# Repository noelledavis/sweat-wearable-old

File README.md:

# Wearable Circuits Documentation

### Table of Contents
1. [What's in the repo?](#toolchain)
2. [Programming Toolchain](#programming)

### What's in the repo?

This repo contains the board designs, firmware, and accompanying documentation for the Eric 4.0 and for the iontophoresis/sweat analysis projects. Documentation for each design is placed in the respective folder, and includes design notes, component datasheets, and programming instructions.

### Programming Toolchain

All of the firmware is written in C++ using the Arduino framework, compiled for the ATMega328P running at 16 MHz on a 5V supply. All of the code can be viewed/edited/compiled in the Arduino IDE (just copy the source into a new sketch).

I have been using [platformio](http://platformio.org/) as my programming toolchain for firmware, and the repo is currently set up for easy compilation and programming using platformio, GNU Make, and the Unix command line. To take advantage of this, install platformio and make sure that the board "pro16MHzatmega328" is installed. After installing platformio, you can use Make to compile the code and to program the microcontroller directly from the command line.

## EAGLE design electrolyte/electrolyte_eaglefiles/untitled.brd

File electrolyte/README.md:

# Iontophoresis + Electrolyte Board Documentation

## Table of Contents
1. [What's in here?](#what)
2. [How to use the board](#how)
3. [Board Architecture](#boardarch)
4. [Physical board layout](#replace)
5. [Firmware and command spec](#command)
6. [Programming instructions](#program)

## What's in here? <div id='what'/>

This folder contains the board design and all of the supporting information for ordring more copies of the iontohphoresis + electrolyte sensing board. It also conatains the firmware for the board, and the datasheets for all of the components.

* **electrolyte_board_datasheets** contains the datasheets for all of the components
* **electrolyte_r3_orderfiles** contains the files needed to order and auto-assemble another round of the iontophoresis + electrolyte board. Included are the gerber files, as well as the centroids file and the Bill of Materials.
* **electrolyte_firmware_FINAL** contains the firmware for the board
* **electrolyte_eaglefiles** contains the Eagle CAD files for the board design. The associated libraries are found in the parent folder under **../eagle_libs**.

## How to use the board? <div id='how'/>

### Supplying power

The board is powered off of a single 3.7V battery, or by a power supply with a minimum output voltage of around 3.5V. **Take care to not let the battery voltage fall too far, as one of the switching regulators on the board has the tendency to heat up a lot if its input voltage is too low.** The current draw on a 4V power supply should be around 0.1A. The pinout for the battery connector is shown below:

### Connecting to Bluetooth

The board can be connected to using Bluetooth (both the GetBlue app and the custom app should work). The baud rate is 9600, and this cannot be changed. Data should be streaming out of the board as soon as a connection is made. The default pairing password for these Bluetooth modules is 1234.

**When trying to control the board using the GetBlue app, make sure that the output of GetBlue is hexadecimal.**

### Using Bluetooth commands

The board receives 8-bit commands over Bluetooth. The baud rate is 9600. When transmitting Bluetooth commands make sure that the commands are sent as bytes or hex values. Sending data as a string will be misinterpreted. The commands have format

The opcode determines what the command is, and the payload is a 4-bit number containing data. 

The board has two modes, sensing mode and current mode:

#### Sensing mode

In sensing mode, the board continuously dumps out sensor readings and current values in text string lines with the format

```
SensorCh1,SensorCh2,Current delivered,Current register
```

In this mode, the sensing switches are closed, enabling sensing, and the iontophoresis switches are open, for safety. The sensor readings are valid, the current delivered should be near zero, and current register should be exactly zero. The sensor readings are given in millivolts (mV), and the current delivered reading is given in microamps (uA).

#### Current mode

In current mode, the board continuously dumps out current values and placeholders for sensor readings in the format

```
x,x,Current delivered,Current register
```

In this mode, the sensing switches are open, disabling sensing, and the iontophoresis switches are closed. The current delivered is proportional to the 8-bit current register value. The current delivered reading is given in microamps (uA).

#### Bluetooth command specifications

Name                                   |  Hex   | Function
:-------------------------------------:|:------:|:-------------------------:
DISABLE\_IONTOPHORESIS                 |  0x4   | Disables iontophoresis, puts the board back into sensing mode.
ENABLE\_IONTOPHORESIS\_INCREMENT\_BY   | 0x5    | Adds the payload bits to the iontophoresis PWM value. Has overflow protection. Puts the board into iontophoresis mode automatically.
ENABLE\_IONTOPHORESIS\_DECREMENT\_BY   | 0x6    | Subtracts the payload from the iontophoresis PWM value. Has underflow protection. Takes the board into sensing mode automatically if PWM value reaches 0.

### Which channel is which?

Looking down from the top, with components facing up:

## Board Architecture <div id='boardarch'/>

### Voltage channels

The board has two voltage sensor channels. The analog supply voltage VDDA is 5V. The voltage sensor channels have the following architecture.

The frontend instrumentation amplifier is an Analog Devices AD8422, which was chosen specifically for its low input bias current and corresponding very high input impedance. The - terminal of the instrumentation amplifier is "floating", and is held to near 2.5V by a 10k resistor. This resistor was chosen empirically, and is large enough to be swapped by hand (described later). The reference terminal of the instrumentation amplifier is held to 2.5V to center the output of the instrumentation amplifier around 2.5V (i.e. a 0V difference across the sensor will lead to an output of 2.5V at the instrumentation amplifier). The gain resistor is chosen to be 5k, for an approximate voltage gain of 5.

The second stage of the circuit consists of two cascaded Sallen-Key low-pass filters. The passives are set such for a fourth-order low pass filter with the cutoff frequency set at 1Hz. The op-amps for the filters were chosen to be LT6005 quad general-purpose op-amps, chosen mainly for low power consumption and small size. The output of the second stage is connected directly to one of the channels of the ATMega328P ADC.

The switches placed in front of the instrumentation amplifer input terminals are ADG711 analog switches. **These switches are required to be in the OPEN state when iontophoresis is being run, to eliminate the risk of skin burns through the sensing electrodes**. The ADG711 was chosen for its ultra-low source-drain leakage current, which is necessary for the sensors to function properly.

### Power distribution

The overall system is powered off of a single 3.7V lithium ion battery. The following figure shows the power distribution for the system:

* An LTC3525-5 switching regulator is connected to the battery, and outputs 5V. This regulator is used to power both the analog components and the digital components.
* One TLE2426 rail-splitter. This is connected to the output of the 5V 
voltage regulator to provide virtual ground at 2.5V.
* A 3.3V LDO regulator is connected to the battery, and is used to power the Bluetooth module.
* An LMR64010 boost regulator is connected to the battery, and the feedback resistors are set such that the component outputs +40V for the iontophoresis power supply.

### Iontophoresis current source

The iontophoresis current source consists of a current DAC controlled by a PWM voltage output from the microcontroller. The overall schematic for the iontophoresis current source is shown below:

The PWM output from the microcontroller is passed through a second order low pass filter and then buffered. This serves to convert the PWM wave into its DC average value, and acts as a low-frequency voltage DAC for driving the current DAC. 

The difference amp and output BJT act as a voltage-controlled current source. The arithmetic demonstrating this is worked out in currentsource.pdf.

At the output of the current source, a high-side shunt amplifier based on the INA282 is used to monitor the current in real time. The output of the INA282 is connected to one of the channels of the microcontroller ADC, and is used to make sure that the true output of the current source circuit is close to its programmed value.

A current-limiting circuit is placed after the shunt amplifier, consisting of the MMBF5457 JFET and a series resistor. To raise the current limit, this resistor's value can be set lower (i.e. around 250 Ohm). To lower the current limit, the resistor's value can be set higher (up to around 750 Ohm).

Lastly, an analog switch is placed after the current-limiting circuit, to ensure that current can be fully shut off and to ensure that the iontophoresis circuit does not affect the sensors. The switch was chosen to be an ADG5401, because of its large range of supply voltages (up to 40V). Note that the node at the output of the iontophoresis circuit can swing up as high as around 36V with an open circuit load.

The current DAC can output around 1.2 mA for a wide range of physiological load resistances.

### Bluetooth

The Bluetooth module is an HC-06. These particular modules are quite common among hobbyists, and can be easily obtained off of Amazon. The Bluetooth modules enter bypass mode as soon as a connection is made, so nothing clever needs to be done in the ATMega328P firmware to get the Bluetooth module to work. The baud rate is 9600.

## Board layout <div id='replace'/>

The overall board layout is shown below:

### User replaceable parts

* The Bluetooth module must be hand-installed. The HC-06 Bluetooth module usually comes soldered to a larger baseboard, and you must first desolder the module from the baseboard before installing it onto the iontophoresis + electrolyte board.
* Resistor R27 is the resistor used to set the current limit. By default, this resistor is around 250 Ohm, but can be raised higher (up to around 750 Ohm) for a lower current limit. 

## Firmware and command spec <div id='command'/>

The commands for controlling the electrolyte board over Bluetooth are described in the document **electrolyte_bt_commands/bluetooth_spec.pdf**. Note that the commands consist of two hexadecimal digits. The first hexadecimal digit corresponds to an opcode, and the second hexadecimal digit usually corresponds to an immediate.

The firmware is written like a finite-state-machine. The state variables are
* `iontophoresisStatsuBits`, corresponding to a bitmask determining whether iontophoresis is enabled or not. This state variable affects the states of the switches.
* `measurementStatusBits`, corresponding to a bitmask determining what ADC values to read back, if any.
* `iontophoresisCurrentValue`, corresponding to the 8-bit number (0-255) proportional to the amount of iontophoresis current that should be delivered.

The inputs to the FSM are the commands.

## Programming instructions <div id='program'/>

There are six header pads directly underneath the microcontroller. **Flipping over the board**, and placing it in the orientation described in the image on the left,

Board bottom pinout                             |  Sparkfun Programmer
:----------------------------------------------:|:-------------------------:
  |  

connect the pins of the programmer to the correspondingly labeled pads. **Note that the layout of the programmer pins is different from that of the Eric4.0.** You will most likely have to solder wires to the pads on the amplifier board to achieve this. I suggest using female jumper wires to connect the programmer to these wires. The image on the right shows the pinout of the Sparkfun programmer board.

Open up the Arduino IDE, and make sure the following things are set:
* Board is set to "Arduino Pro" or "Arduino Pro Mini"
* Programmer is USBtinyISP
* Processor is set to ATMega328, 5V 16MHz

If you are programming a board for the very first time, make sure you run "Burn the Bootloader" or else the code won't work. This seems to be the most foolproof way to make sure that the fuses are set to the correct values.

Then, from the Arduino IDE, you can click "Upload using programmer" to put the code onto the microcontroller.

Alternatively, if you have platformio and GNU Make installed, you can run
```
make
```
to compile the code and
```
make impact
```
to copy the code onto the microcontroller. **I have not figured out how to burn fuse values through platformio, so you're going to have to open up the Arduino IDE to do that.**

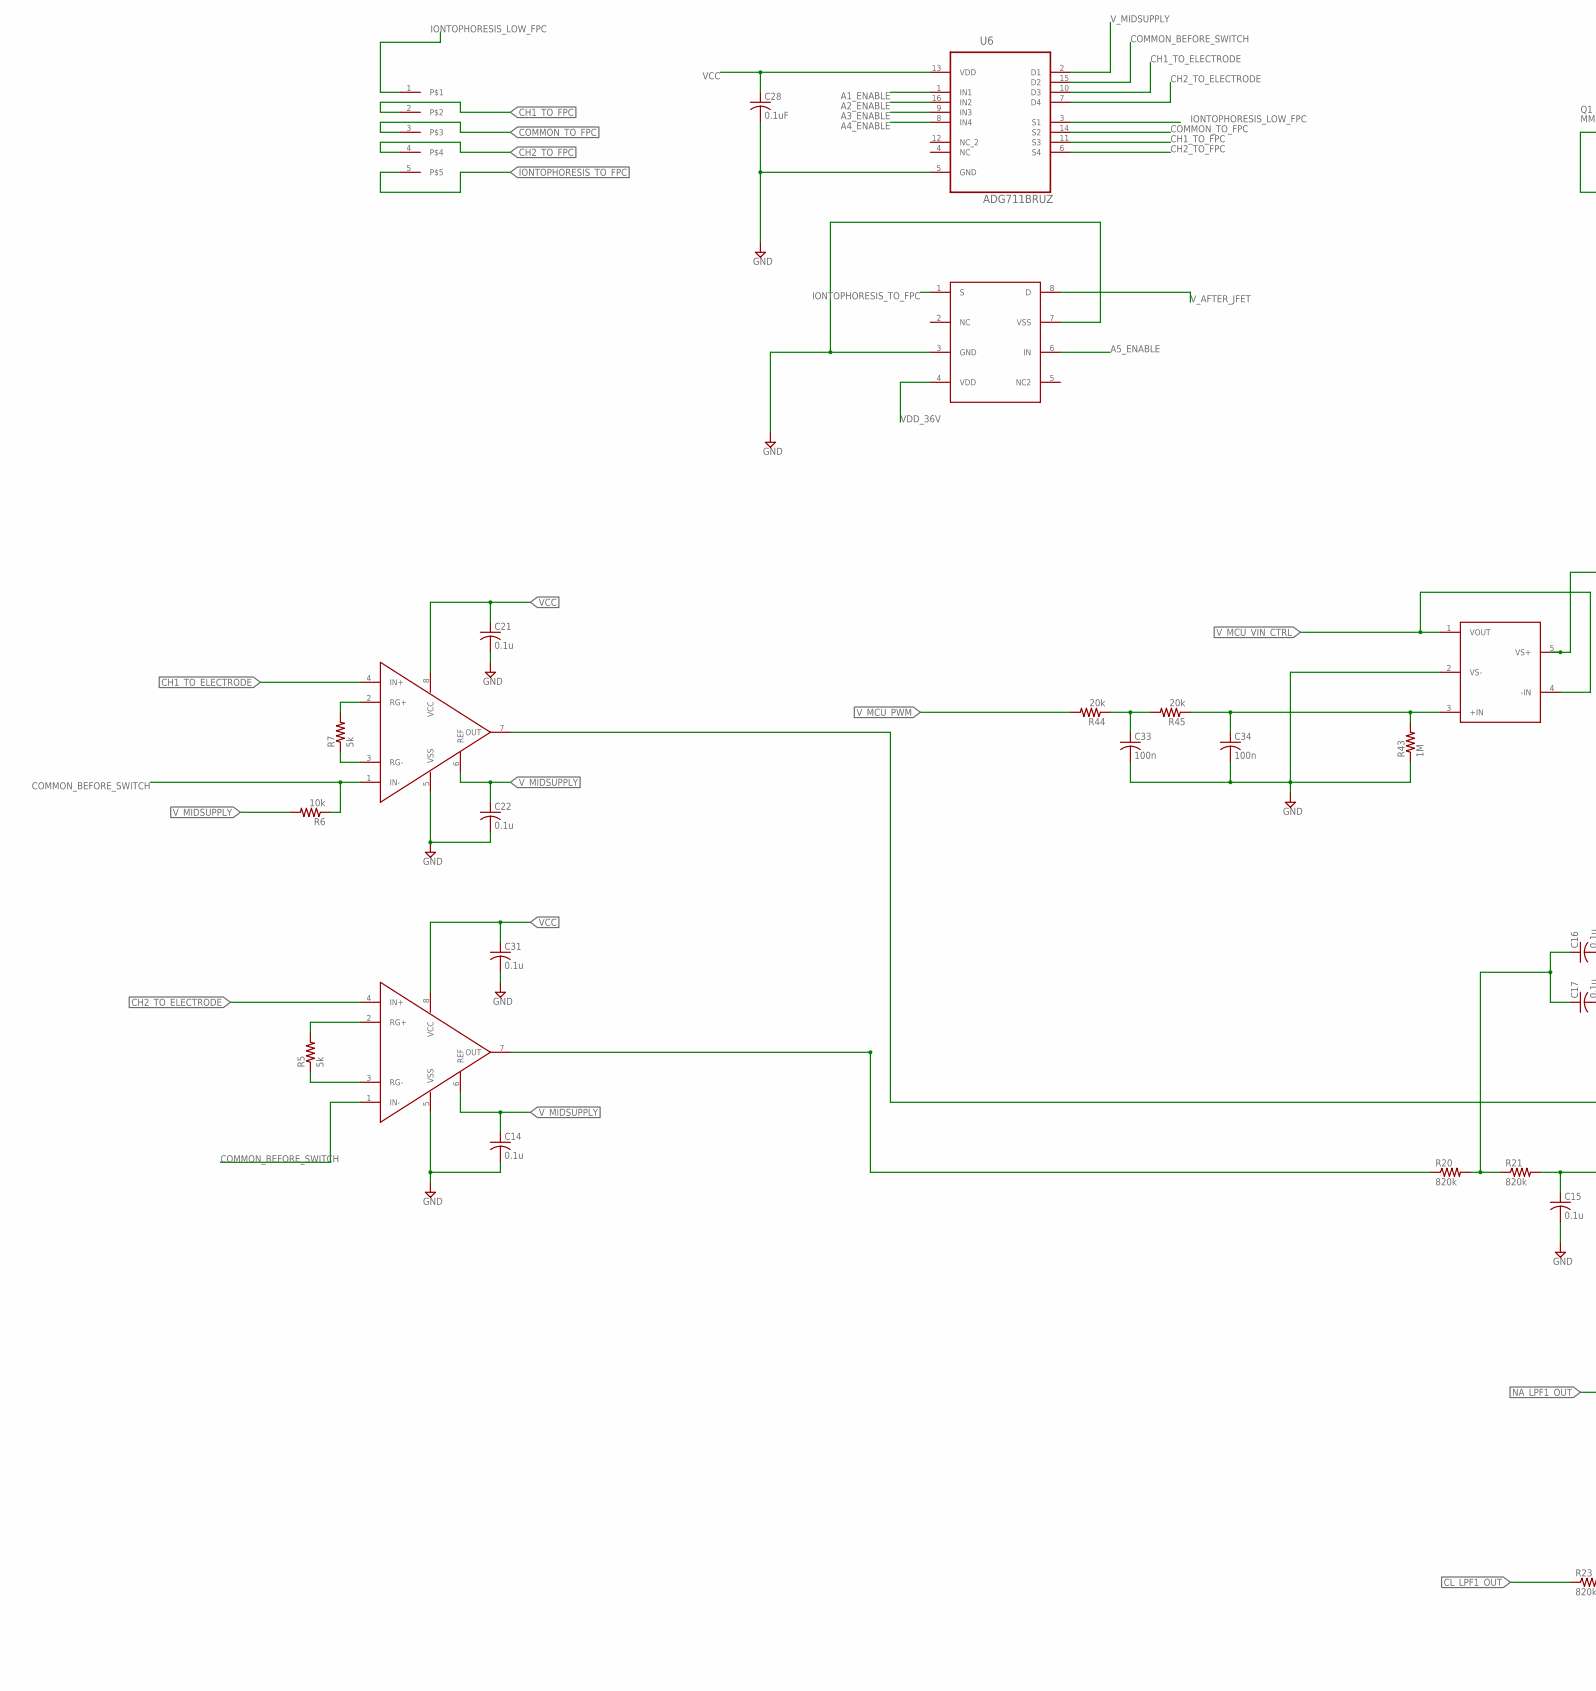
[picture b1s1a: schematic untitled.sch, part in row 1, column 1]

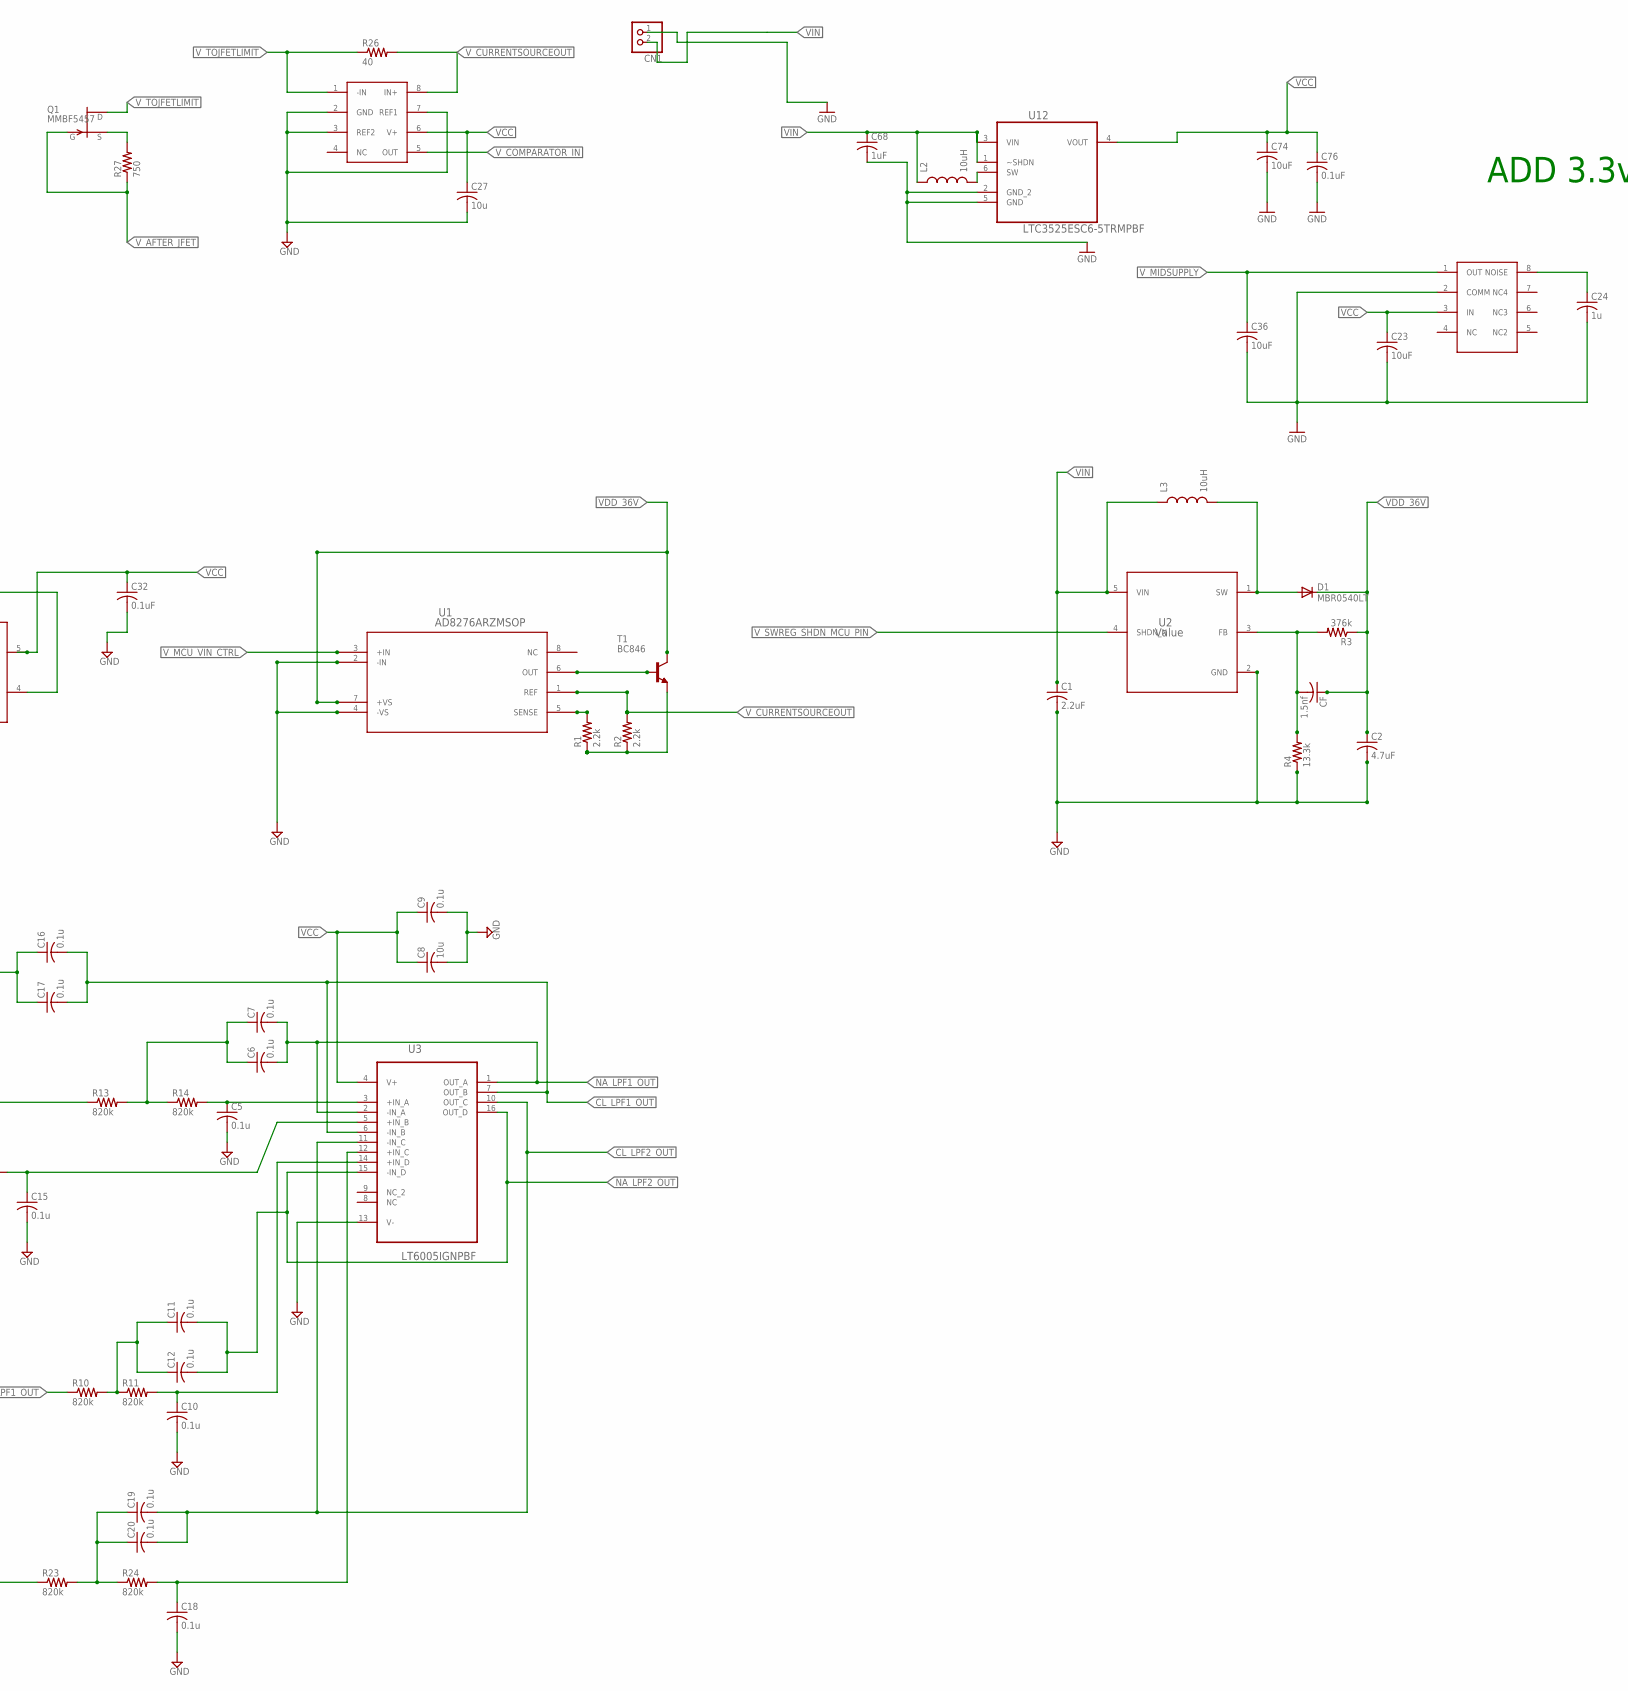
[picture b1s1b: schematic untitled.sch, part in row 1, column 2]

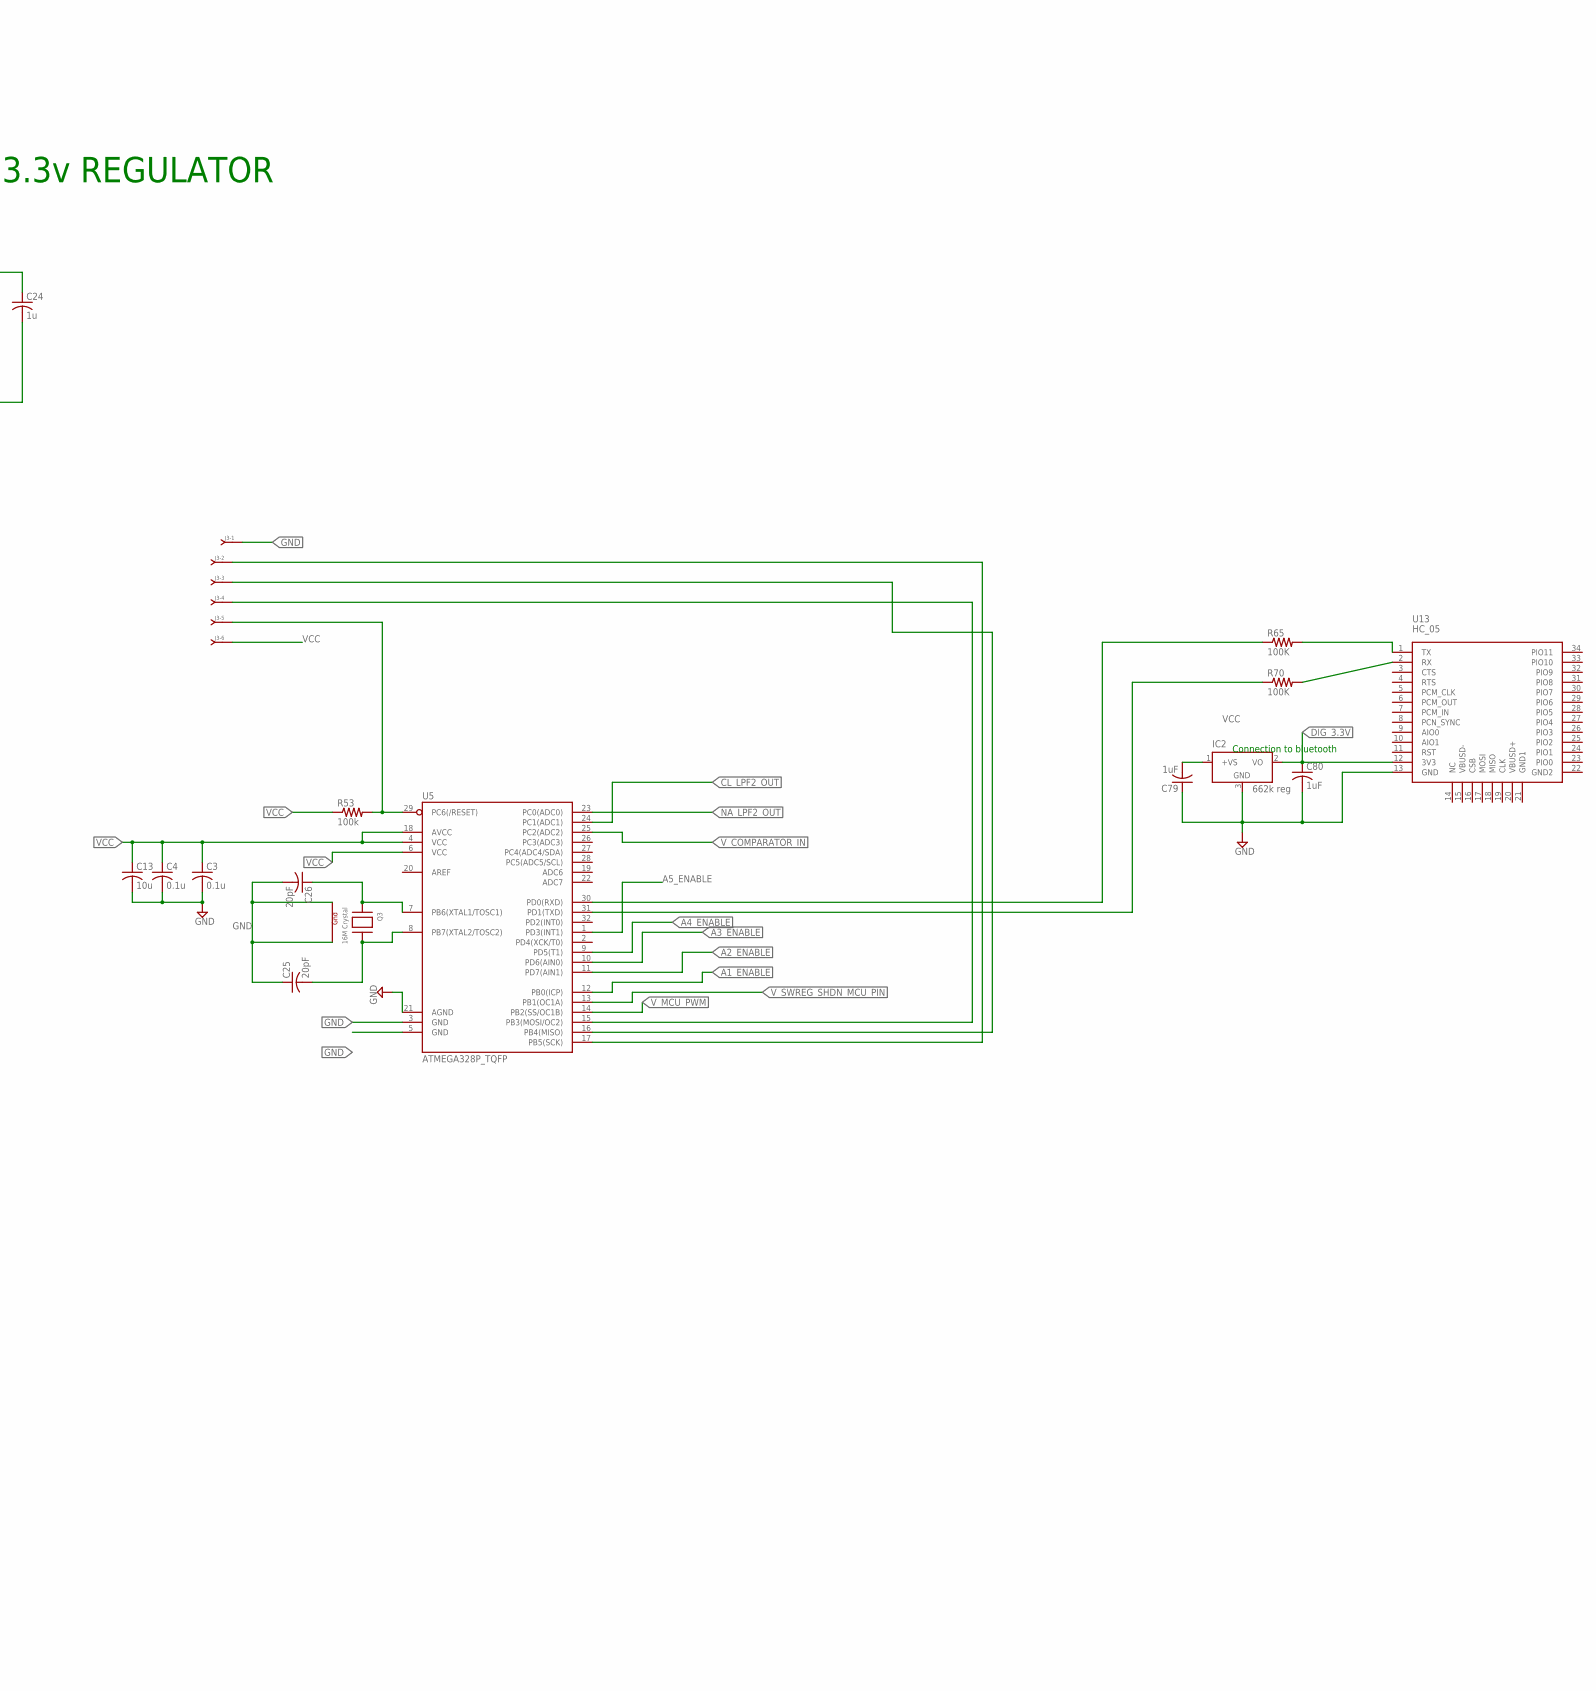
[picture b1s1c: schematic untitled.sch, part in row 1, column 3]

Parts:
C1: 2.2uF; C0402
C2: 4.7uF; C0603
C3, C4, C5, C6, C7, C9, C10, C11, C12, C14, C15, C16, C17, C18, C19, C20, C21, C22, C31: 0.1u; C0201
C8, C13, C27: 10u; C0402
C23, C36, C74: 10uF; C0402
C24: 1u; C0402
C25, C26: 20pF; C0402
C28, C32: 0.1uF; C0201
C33, C34: 100n; C0201
C68, C79, C80: 1uF; C0402; MPN MC0402X105M6R3CT
C76: 0.1uF; C0402
CF: 1.5nf; C0402
CN1: JST_2PIN-SMT; JST-PH-2-SMT
D1: MBR0540LT; SOD123
IC2: 662k reg; SOT23; MPN LM5008MM/NOPB
J3: J-06-100-2X03; HDR-100-2X03
L2, L3: 10uH; 0805
Q1: MMBF5457; SOT23
Q3: 16M Crystal; NX3225
R1, R2: 2.2k; R0201
R3: 376k; R0402
R4: 13.3k; R0402
R5, R7: 5k; R0201
R6: 10k; R0201
R10, R11, R13, R14, R20, R21, R23, R24: 820k; R0201
R26: 40; R0201
R27: 750; R0402
R43: 1M; R0201
R44, R45: 20k; R0201
R53: 100k; R0201
R65, R70: 100K; R0201
T1: BC846; SOT23
U1: AD8276ARZMSOP; MSOP08
U2: Value; DBV0005A_N
U3: LT6005IGNPBF; SOP63P600X175-16N
U4: INA282; SO08
U5: ATMEGA328P_TQFP; TQFP32-08
U6: ADG711BRUZ; SOP65P640X120-16N
U7, U8: SOIC8_INAMPMSOP; MSOP08
U12: LTC3525ESC6-5TRMPBF; SOT65P210X100-6N
U13: HC_05; BLUETOOTH_SMD
U15: TLE2426IDR; R_8
U20: FH12-5S-1SH
U$1: ADG5401; MSOP08
U$5: LT1800; SOT23-5

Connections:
A1_ENABLE: U5.12 (PB0(ICP)), U6.1 (IN1)
A2_ENABLE: U5.11 (PD7(AIN1)), U6.16 (IN2)
A3_ENABLE: U5.10 (PD6(AIN0)), U6.9 (IN3)
A4_ENABLE: U5.9 (PD5(T1)), U6.8 (IN4)
A5_ENABLE: U5.1 (PD3(INT1)), U$1.6 (IN)
CH1_TO_ELECTRODE: U6.10 (D3), U7.4 (IN+)
CH1_TO_FPC: U6.11 (S3), U20.2
CH2_TO_ELECTRODE: U6.7 (D4), U8.4 (IN+)
CH2_TO_FPC: U6.6 (S4), U20.4
CL_LPF1_OUT: C16.2, C17.2, R23.1, U3.6 (-IN_B), U3.7 (OUT_B)
CL_LPF2_OUT: C19.2, C20.2, U3.10 (OUT_C), U3.11 (-IN_C), U5.24 (PC1(ADC1))
COMMON_BEFORE_SWITCH: R6.1, U6.15 (D2), U7.1 (IN-), U8.1 (IN-)
COMMON_TO_FPC: U6.14 (S2), U20.3
DIG_3.3V: C80.1, IC2.2 (VO), U13.12 (3V3)
GND: C1.2, C2.2, C3.2, C4.2, C5.2, C8.2, C9.2, C10.2, C13.2, C14.2, C15.2, C18.2, C21.2, C22.2, C23.2, C24.2, C25.1, C26.2, C27.2, C28.2, C31.2, C32.2, C33.2, C34.2, C36.2, C68.2, C74.2, C76.2, C79.1, C80.2, CN1.1 (2), IC2.3 (GND), J3.1, Q3.2 (G2), Q3.4 (G1), R4.1, R43.1, U1.2 (-IN), U1.4 (-VS), U2.2 (GND), U3.13 (V-), U4.2 (GND), U4.3 (REF2), U4.7 (REF1), U5.3 (GND), U5.5 (GND), U5.21 (AGND), U6.5 (GND), U7.5 (VSS), U8.5 (VSS), U12.2 (GND_2), U12.5 (GND), U13.13 (GND), U15.2 (COMM), U$1.3 (GND), U$1.7 (VSS), U$5.2 (VS-)
IONTOPHORESIS_LOW_FPC: U6.3 (S1), U20.1
IONTOPHORESIS_TO_FPC: U20.5, U$1.1 (S)
unnamed: T1.1 (B), U1.6 (OUT)
unnamed: R13.1, U7.7 (OUT)
unnamed: R1.2, U1.5 (SENSE)
unnamed: R1.1, R2.1, T1.2 (E)
unnamed: R20.1, U8.7 (OUT)
unnamed: R5.1, U8.3 (RG-)
unnamed: CF.2, R3.2, R4.2, U2.3 (FB)
unnamed: R5.2, U8.2 (RG+)
unnamed: R65.1, U5.30 (PD0(RXD))
unnamed: C10.1, R11.2, U3.14 (+IN_D)
unnamed: C5.1, R14.2, U3.3 (+IN_A)
unnamed: Q1.2 (S), R27.2
unnamed: C6.1, C7.1, R13.2, R14.1
unnamed: C11.1, C12.1, R10.2, R11.1
unnamed: R7.1, U7.3 (RG-)
unnamed: R7.2, U7.2 (RG+)
unnamed: C24.1, U15.8 (NOISE)
unnamed: C15.1, R21.2, U3.5 (+IN_B)
unnamed: C16.1, C17.1, R20.2, R21.1
unnamed: C18.1, R24.2, U3.12 (+IN_C)
unnamed: C19.1, C20.1, R23.2, R24.1
unnamed: J3.5, R53.2, U5.29 (PC6(/RESET))
unnamed: L2.2, U12.6 (SW)
unnamed: C25.2, Q3.3 (X2), U5.8 (PB7(XTAL2/TOSC2))
unnamed: C34.1, R43.2, R45.1, U$5.3 (+IN)
unnamed: C33.1, R44.1, R45.2
unnamed: C26.1, Q3.1 (X1), U5.7 (PB6(XTAL1/TOSC1))
unnamed: R65.2, U13.1 (TX)
unnamed: J3.4, U5.15 (PB3(MOSI/OC2))
unnamed: J3.2, U5.17 (PB5(SCK))
unnamed: J3.3, U5.16 (PB4(MISO))
unnamed: R70.1, U5.31 (PD1(TXD))
unnamed: R70.2, U13.2 (RX)
NA_LPF1_OUT: C6.2, C7.2, R10.1, U3.1 (OUT_A), U3.2 (-IN_A)
NA_LPF2_OUT: C11.2, C12.2, U3.15 (-IN_D), U3.16 (OUT_D), U5.23 (PC0(ADC0))
PIN1: D1.A, L3.2, U2.1 (SW)
VCC: C3.1, C4.1, C8.1, C9.1, C13.1, C21.1, C23.1, C27.1, C28.1, C31.1, C32.1, C74.1, C76.1, C79.2, IC2.1 (+VS), J3.6, R53.1, U3.4 (V+), U4.6 (V+), U5.4 (VCC), U5.6 (VCC), U5.18 (AVCC), U6.13 (VDD), U7.8 (VCC), U8.8 (VCC), U12.4 (VOUT), U15.3 (IN), U$5.5 (VS+)
VDD_36V: C2.1, CF.1, D1.C, R3.1, T1.3 (C), U1.7 (+VS), U$1.4 (VDD)
VIN: C1.1, C68.1, CN1.2 (1), L2.1, L3.1, U2.5 (VIN), U12.1 (~SHDN), U12.3 (VIN)
V_AFTER_JFET: Q1.3 (G), R27.1, U$1.8 (D)
V_COMPARATOR_IN: U4.5 (OUT), U5.25 (PC2(ADC2))
V_CURRENTSOURCEOUT: R2.2, R26.2, U1.1 (REF), U4.8 (IN+)
V_MCU_PWM: R44.2, U5.14 (PB2(SS/OC1B))
V_MCU_VIN_CTRL: U1.3 (+IN), U$5.1 (VOUT), U$5.4 (-IN)
V_MIDSUPPLY: C14.1, C22.1, C36.1, R6.2, U6.2 (D1), U7.6 (REF), U8.6 (REF), U15.1 (OUT)
V_SWREG_SHDN_MCU_PIN: U2.4 (SHDN_N), U5.13 (PB1(OC1A))
V_TOJFETLIMIT: Q1.1 (D), R26.1, U4.1 (-IN)

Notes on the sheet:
ADD 3.3v REGULATOR
Connection to bluetooth

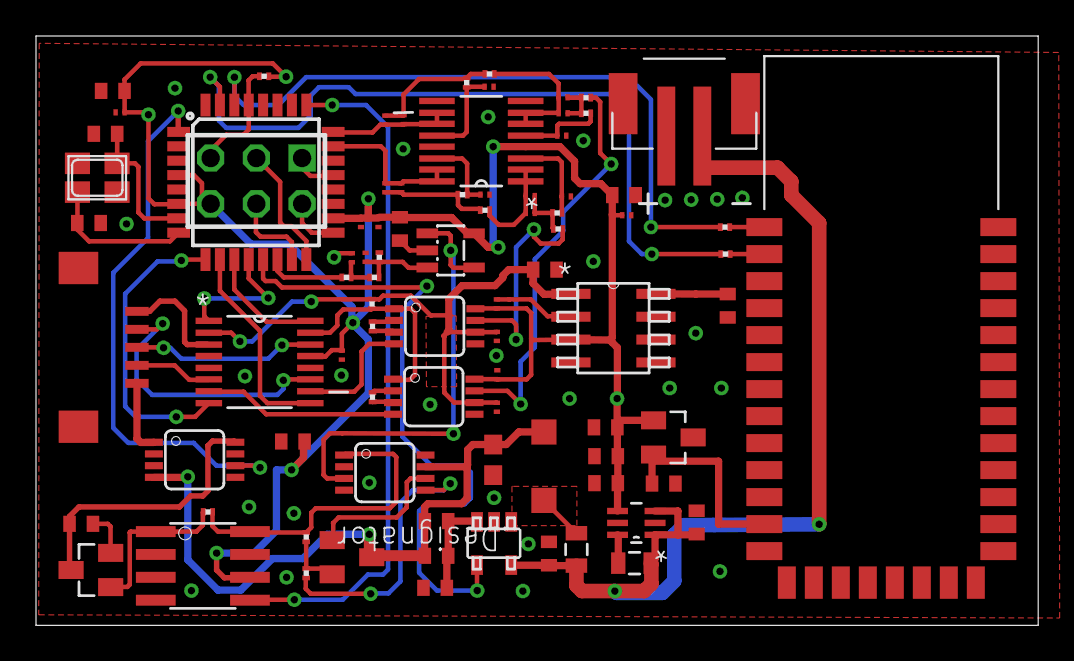
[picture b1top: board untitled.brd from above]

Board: 2 copper layers, 55.7 x 32.7 mm, 85 parts (0 on the bottom side), 64 nets.

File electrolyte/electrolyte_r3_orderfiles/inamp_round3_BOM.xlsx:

Item # | Quantity per board | Manufacturer Part # | Do Not Install | Reference designators | Vendor (optional) | Vendor Part Number (optional) | Value (optional) | Size / Footprint (optional) | Part description/ specs (optional, but recommended) | Manfacturer (optional)
1 | 1 | CRCW02011M00FNED |  | R43 | Digikey | 541-1.00MABCT-ND | 1M | R0201 |  | Vishay-Dale
2 | 1 | MMBF5457 |  | Q1 | Digikey | MMBF5457CT-ND | MMBF5457 N-channel JFET | SOT23 |  | Fairchild
3 | 2 | GRM1555C1H200JA01D |  | C25,C26 | Digikey | 490-5930-1-ND | 20pF | C0402 | 20pF capacitor | Murata
4 | 1 | CL05B152KB5NNNC |  | CF | Digikey | 1276-1521-1-ND | 1500pF | C0402 | 50V 1500pF capacitor | Samsung
5 | 1 | LMR64010XMFE/NOPB |  | U2 | Digikey | LMR64010XMFE/NOPBCT-ND |  | SOT23-5 |  | Texas Instruments
6 | 4 | GRM155R60J105KE19D |  | C24,C68,C79,C80 | Digikey | 490-1320-1-ND | 1uF | C0402 |  | Murata
7 | 1 | INA282AIDR |  | U4 | Digikey | 296-27820-1-ND |  | SOIC-8 |  | Texas Instruments
8 | 1 | LT6005IGN#PBF |  | U3 | Digikey | LT6005IGN#PBF-ND |  | 16-SSOP |  | Linear Technologies
9 | 1 | MBR0540L-TP |  | D1 | Digikey | MBR0540L-TPMSTR-ND |  | SOD123 | 40V Schottky diode | Micro Commercial
10 | 1 | MCR006YRTJ390 |  | R26 | Digikey | RHM39CCCT-ND | 39 | R0201 |  | Rohm Semiconductor
11 | 3 | MCR006YRTF1003 |  | R65,R70,R53 | Digikey | RHM100KCBCT-ND | 100k | R0201 |  | Rohm Semiconductor
12 | 1 | CL05A225MQ5NNNC |  | C1 | Digikey | 1276-1469-1-ND | 2.2uF | C0402 |  | Samsung
13 | 1 | ADG711BRUZ |  | U6 | Digikey | ADG711BRUZ-ND |  | 16TSSOP |  | Analog Devices
14 | 1 | BC846B,215 |  | T1 | Digikey | 568-1632-1-ND |  | SOT23 | 65V NPN BJT | NXP Semiconductors
15 | 1 | FH12-5S-1SH(55) |  | U20 | Digikey | HFB105CT-ND |  |  |  | Hirose
16 | 1 |  | DNI | R27
17 | 2 | MLZ2012M100WTD25 |  | L2,L3 | Digikey | 445-17073-1-ND | 10uH | 805 |  | TDK
18 | 1 | ERJ-2RKF1332X |  | R4 | Digikey | P13.3KLCT-ND | 13.3k | R0402 |  | Panasonic
19 | 6 | CL05A106MQ5NUNC |  | C8,C13,C23,C27,C36,C74 | Digikey | 1276-1451-1-ND | 10uF capacitor | C0402 |  | Samsung
20 | 1 | LTC3525ESC6-5#TRMPBF |  | U12 | Digikey | LTC3525ESC6-5#TRMPBFCT-ND |  | SC70 | 5V boost regulator | Linear Technologies
21 | 1 | LT1800CS5#TRMPBF |  | U$5 | Digikey | LT1800CS5#TRMPBFCT-ND |  | TSOT23-5 |  | Linear Technologies
22 | 8 | ERJ-1GEF8203C |  | R10,R11,R13,R14,R20,R21,R23,R24 | Digikey | P820KABCT-ND | 820k | R0201 |  | Panasonic
23 | 2 | RC0201JR-0720KL |  | R44,R45 | Digikey | 311-20KNCT-ND | 20k | R0201 |  | Yageo
24 | 1 | S2B-PH-SM4-TB(LF)(SN) |  | CN1 | Digikey | 455-1749-1-ND |  |  | JST-PH 2 pin connector | JST
25 | 23 | GRM033R60J104KE19D |  | C3,C4,C5,C6,C7,C9,C10,C11,C12,C14,C15,C16,C17,C18,C19,C20,C21,C22,C31,C32,C33,C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 | Digikey | 490-3167-1-ND | 0.1uF capacitor | C0201 |  | Murata
26 | 1 | ADG5401BRMZ |  | U$1 | Digikey | ADG5401BRMZ-ND |  |  |  | Analog Devices
27 | 1 | AP7313-33SAG-7 |  | IC2 | Digikey | AP7313-33SAG-7DICT-ND |  | SOT23 | 3.3V LDO | Diodes Incorporated
28 | 1 | GRM155R61A104KA01D |  | C76 | Digikey | 490-1318-1-ND | 0.1uF capacitor | C0402 |  | Murata
29 | 1 | C1608X5R1V475M080AC |  | C2 | Digikey | 445-9042-1-ND | 4.7uF capacitor | C0603 | 35V capacitor | TDK
30 | 2 | AD8422BRMZ |  | U7,U8 | Digikey | AD8422BRMZ-ND |  | 8-MSOP | Instrumentation amplifier | Analog Devices
31 | 1 | C0603X5R0J105M030BC |  | C30 | Digikey | 445-8008-1-ND | 1uF capacitor | C0201 |  | TDK
32 | 1 | AD8276ARMZ-R7 |  | U1 | Digikey | AD8276ARMZ-R7TR-ND |  | 8-MSOP |  | Analog Devices
33 | 1 | ATMEGA328P-AUR |  | U5 | Digikey | ATMEGA328P-AURCT-ND |  | 32-TQFP |  | Atmel
34 | 1 | NX3225SA-16.000000MHZ-T1 |  | Q3 | Digikey | 644-1100-1-ND |  |  | 16 MHz oscillator | NDK
35 | 2 | CRCW02012K20FKED |  | R1,R2 | Digikey | 541-2.20KAABCT-ND | 2.2k | R0201 |  | Vishay-Dale
36 | 2 | ERJ-1GEF4991C |  | R5,R7 | Digikey | P4.99KABTR-ND | 4.99k | R0201 |  | Panasonic
37 | 1 | CRCW0402374KFKED |  | R3 | Digikey | 541-374KLCT-ND | 374k | R0402 |  | Vishay-Dale
38 | 1 | TLE2426IDR |  | U15 | Digikey | 296-1345-1-ND |  | 8_SOIC |  | Texas Instruments
39 | 1 | RC0201JR-0710KL |  | R6 | Digikey | 311-10KNCT-ND | 10k | R0201 | 10k | Yageo
40 | 1 |  | DNI | U13

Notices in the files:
parts and their libraries:
SparkFun-Passives: Licensing: Creative Commons ShareAlike 4.0 International - https://creativecommons.org/licenses/by-sa/4.0
con-headers-jp: Copyright (C) 2008, Bob Starr
